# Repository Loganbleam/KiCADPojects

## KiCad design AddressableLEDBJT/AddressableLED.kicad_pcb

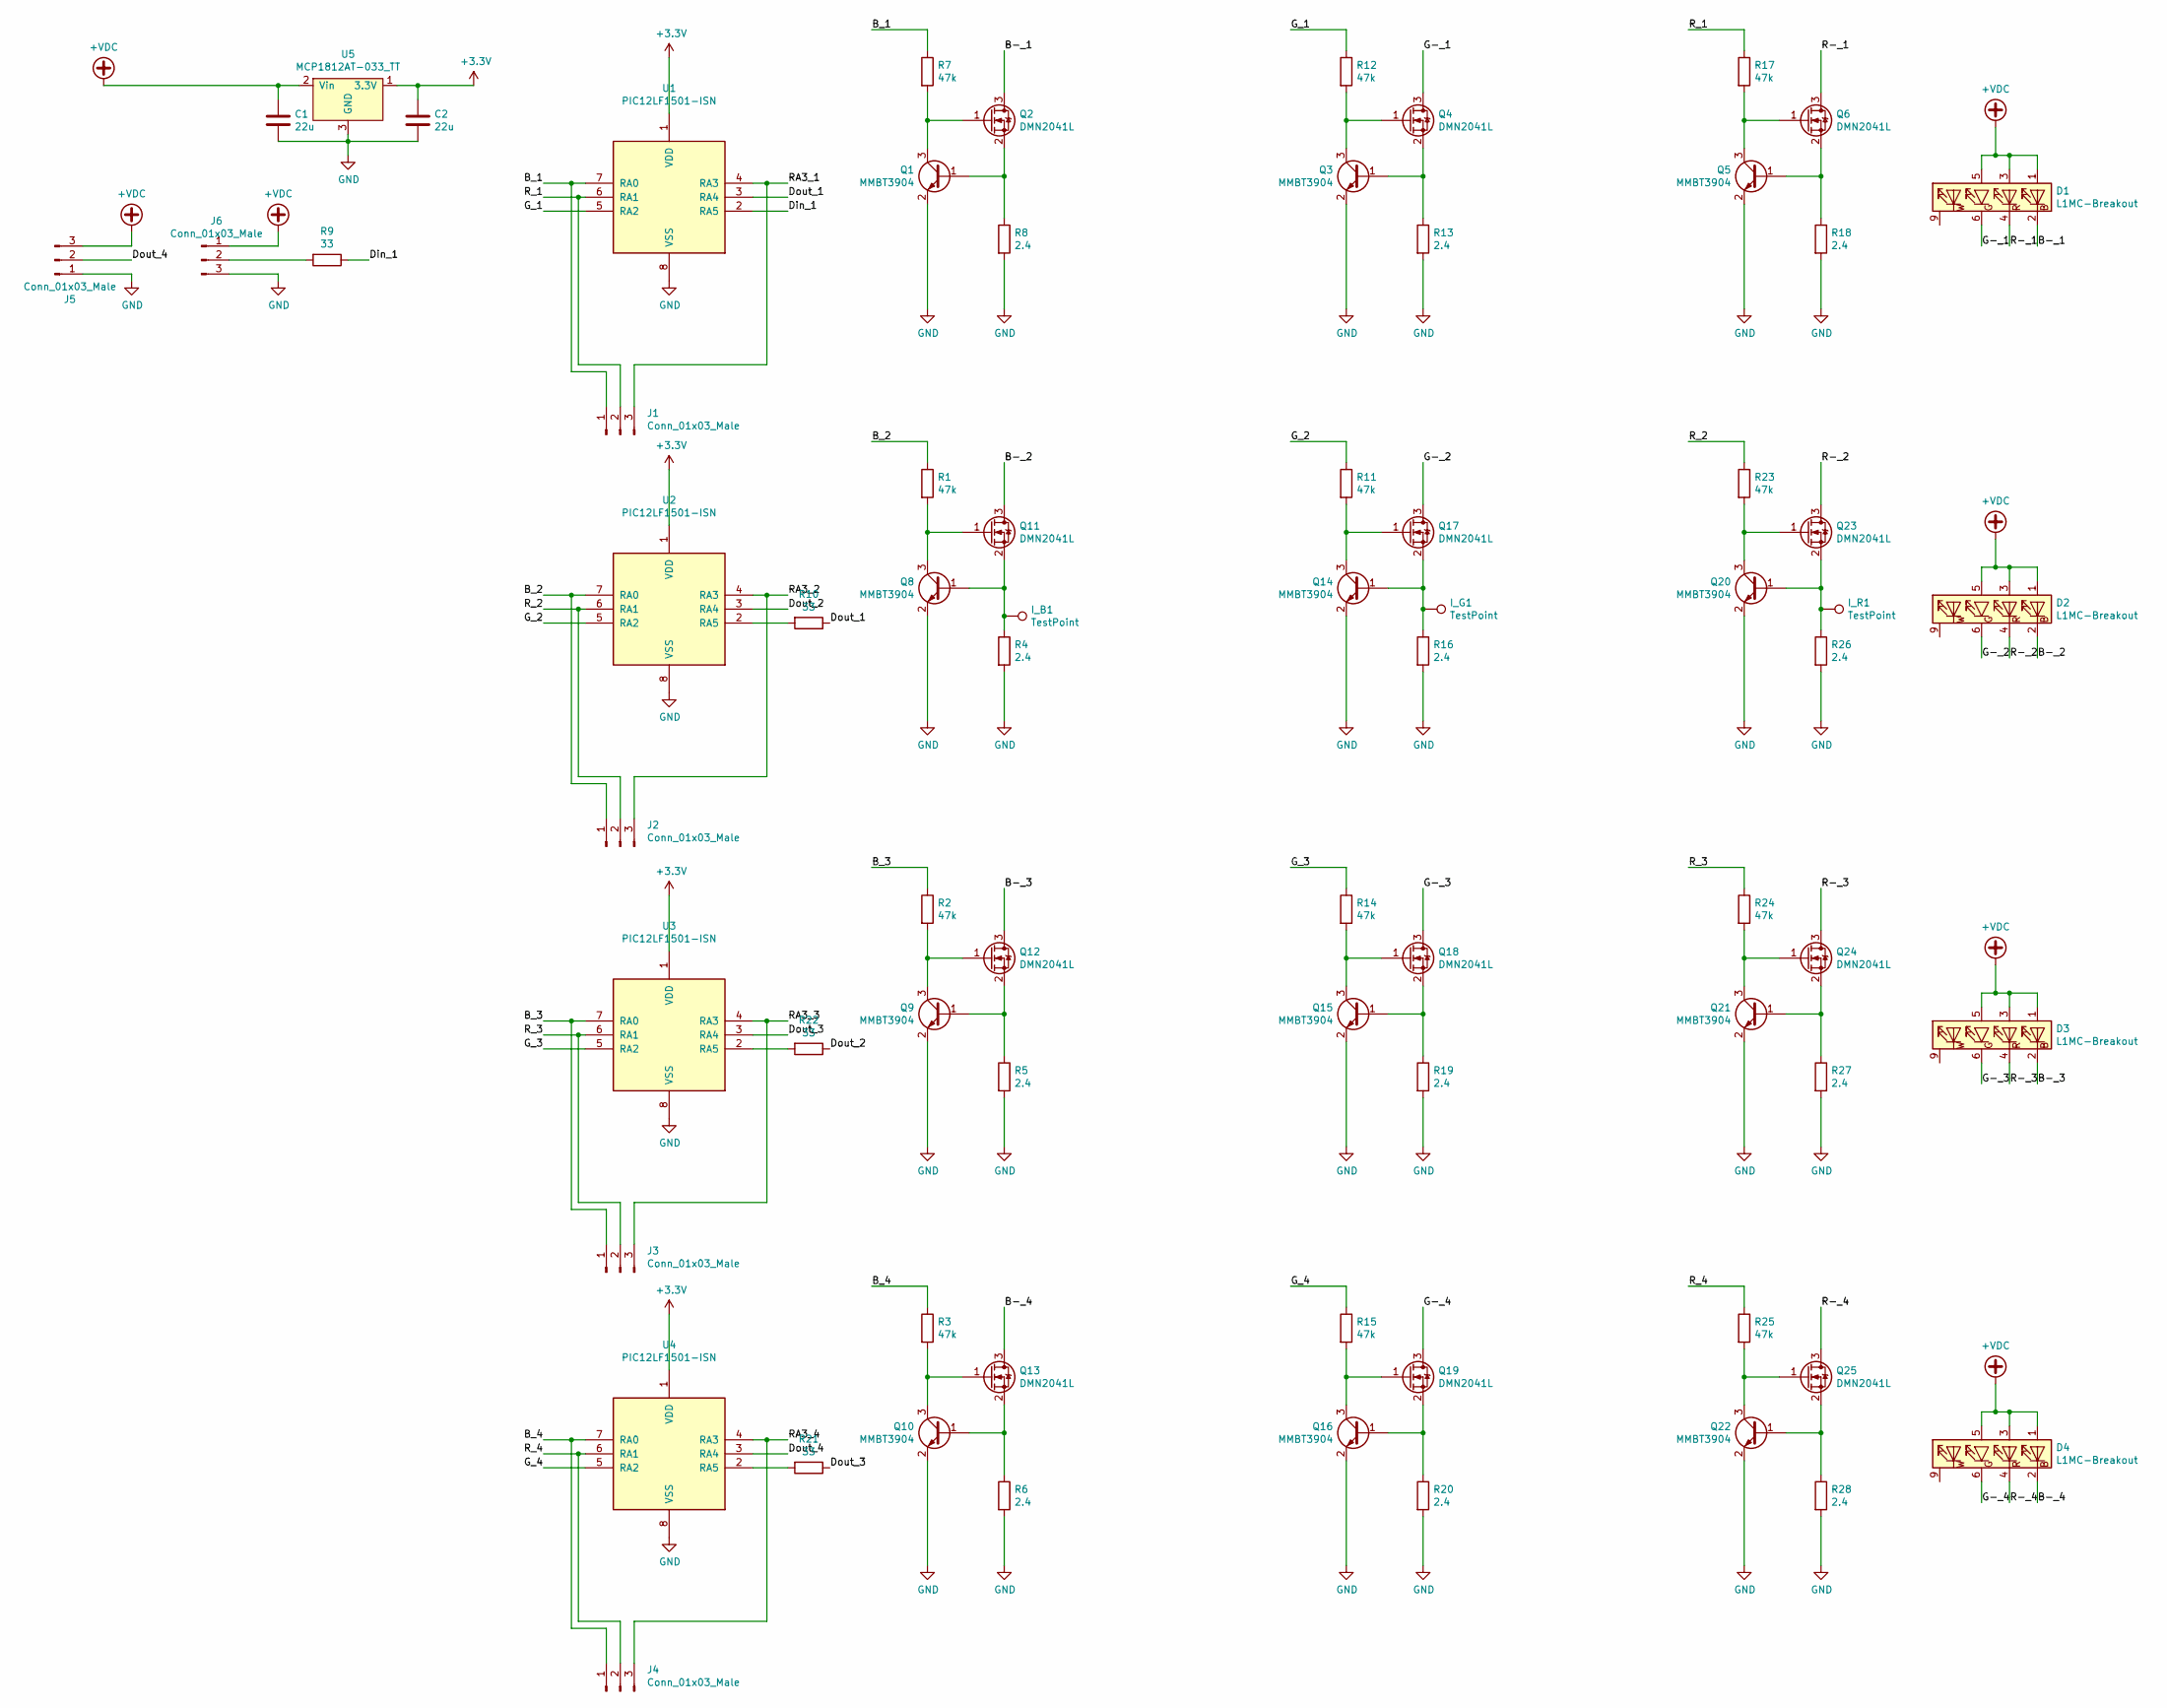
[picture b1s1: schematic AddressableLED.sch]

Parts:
C1, C2: 22u; C_0603_1608Metric
D1, D2, D3, D4: L1MC-Breakout; L1MC-RGB3080
I_B1: TestPoint; TestPoint_Pad_D1.0mm
I_G1: TestPoint; TestPoint_Pad_D1.0mm
I_R1: TestPoint; TestPoint_Pad_D1.0mm
J1, J2, J3, J4: Conn_01x03_Male; PinHeader_1x03_P1.00mm_Vertical
J5, J6: Conn_01x03_Male; JST_VH_B3P-VH-B_1x03_P3.96mm_Vertical
Q1, Q3, Q5, Q8, Q9, Q10, Q14, Q15, Q16, Q20, Q21, Q22: MMBT3904; SOT-23
Q2, Q4, Q6, Q11, Q12, Q13, Q17, Q18, Q19, Q23, Q24, Q25: DMN2041L; SOT-23
R1, R2, R3, R7, R11, R12, R14, R15, R17, R23, R24, R25: 47k; R_0603_1608Metric
R4, R5, R6, R8, R13, R16, R18, R19, R20, R26, R27, R28: 2.4; R_0805_2012Metric
R9, R10, R21, R22: 33; R_0603_1608Metric
U1, U2, U3, U4: PIC12LF1501-ISN; DFN-8-1EP_3x3mm_P0.65mm_EP1.7x2.05mm
U5: MCP1812AT-033_TT; SOT-23

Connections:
+3V3: C2.1, U1.1 (VDD), U2.1 (VDD), U3.1 (VDD), U4.1 (VDD), U5.1 (3.3V)
+VDC: C1.1, D1.1 (B+), D1.3 (R+), D1.5 (G+), D2.1 (B+), D2.3 (R+), D2.5 (G+), D3.1 (B+), D3.3 (R+), D3.5 (G+), D4.1 (B+), D4.3 (R+), D4.5 (G+), J5.3, J6.1, U5.2 (Vin)
/B-_1: D1.2 (B-), Q2.3 (D)
/B-_2: D2.2 (B-), Q11.3 (D)
/B-_3: D3.2 (B-), Q12.3 (D)
/B-_4: D4.2 (B-), Q13.3 (D)
/B_1: J1.1, R7.1, U1.7 (RA0)
/B_2: J2.1, R1.1, U2.7 (RA0)
/B_3: J3.1, R2.1, U3.7 (RA0)
/B_4: J4.1, R3.1, U4.7 (RA0)
/Din_1: R9.1, U1.2 (RA5)
/Dout_1: R10.1, U1.3 (RA4)
/Dout_2: R22.1, U2.3 (RA4)
/Dout_3: R21.1, U3.3 (RA4)
/Dout_4: J5.2, U4.3 (RA4)
/G-_1: D1.6 (G-), Q4.3 (D)
/G-_2: D2.6 (G-), Q17.3 (D)
/G-_3: D3.6 (G-), Q18.3 (D)
/G-_4: D4.6 (G-), Q19.3 (D)
/G_1: R12.1, U1.5 (RA2)
/G_2: R11.1, U2.5 (RA2)
/G_3: R14.1, U3.5 (RA2)
/G_4: R15.1, U4.5 (RA2)
/R-_1: D1.4 (R-), Q6.3 (D)
/R-_2: D2.4 (R-), Q23.3 (D)
/R-_3: D3.4 (R-), Q24.3 (D)
/R-_4: D4.4 (R-), Q25.3 (D)
/RA3_1: J1.3, U1.4 (RA3)
/RA3_2: J2.3, U2.4 (RA3)
/RA3_3: J3.3, U3.4 (RA3)
/RA3_4: J4.3, U4.4 (RA3)
/R_1: J1.2, R17.1, U1.6 (RA1)
/R_2: J2.2, R23.1, U2.6 (RA1)
/R_3: J3.2, R24.1, U3.6 (RA1)
/R_4: J4.2, R25.1, U4.6 (RA1)
GND: C1.2, C2.2, J5.1, J6.3, Q1.2 (E), Q3.2 (E), Q5.2 (E), Q8.2 (E), Q9.2 (E), Q10.2 (E), Q14.2 (E), Q15.2 (E), Q16.2 (E), Q20.2 (E), Q21.2 (E), Q22.2 (E), R4.2, R5.2, R6.2, R8.2, R13.2, R16.2, R18.2, R19.2, R20.2, R26.2, R27.2, R28.2, U1.8 (VSS), U2.8 (VSS), U3.8 (VSS), U4.8 (VSS), U5.3 (GND)
unnamed: I_B1.1, Q8.1 (B), Q11.2 (S), R4.1
unnamed: I_G1.1, Q14.1 (B), Q17.2 (S), R16.1
unnamed: I_R1.1, Q20.1 (B), Q23.2 (S), R26.1
unnamed: J6.2, R9.2
unnamed: Q1.1 (B), Q2.2 (S), R8.1
unnamed: Q1.3 (C), Q2.1 (G), R7.2
unnamed: Q3.1 (B), Q4.2 (S), R13.1
unnamed: Q3.3 (C), Q4.1 (G), R12.2
unnamed: Q5.1 (B), Q6.2 (S), R18.1
unnamed: Q5.3 (C), Q6.1 (G), R17.2
unnamed: Q10.1 (B), Q13.2 (S), R6.1
unnamed: Q10.3 (C), Q13.1 (G), R3.2
unnamed: Q8.3 (C), Q11.1 (G), R1.2
unnamed: Q9.3 (C), Q12.1 (G), R2.2
unnamed: Q9.1 (B), Q12.2 (S), R5.1
unnamed: Q14.3 (C), Q17.1 (G), R11.2
unnamed: Q15.1 (B), Q18.2 (S), R19.1
unnamed: Q15.3 (C), Q18.1 (G), R14.2
unnamed: Q16.1 (B), Q19.2 (S), R20.1
unnamed: Q16.3 (C), Q19.1 (G), R15.2
unnamed: Q20.3 (C), Q23.1 (G), R23.2
unnamed: Q21.1 (B), Q24.2 (S), R27.1
unnamed: Q21.3 (C), Q24.1 (G), R24.2
unnamed: Q22.1 (B), Q25.2 (S), R28.1
unnamed: Q22.3 (C), Q25.1 (G), R25.2
unnamed: R10.2, U2.2 (RA5)
unnamed: R21.2, U4.2 (RA5)
unnamed: R22.2, U3.2 (RA5)

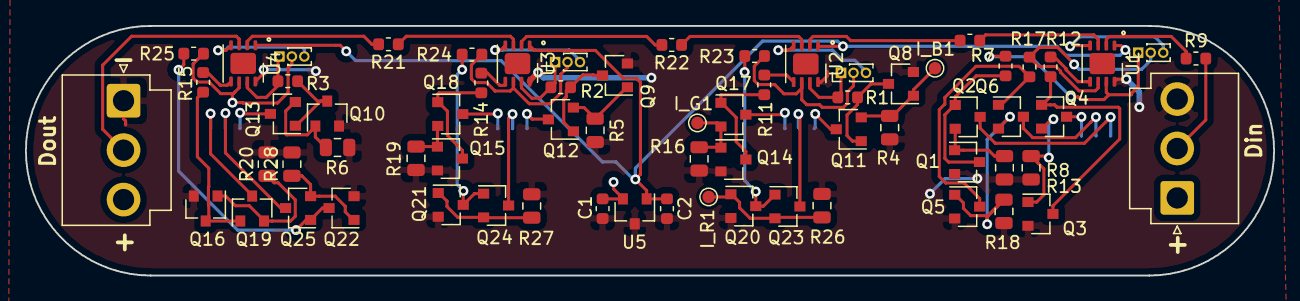
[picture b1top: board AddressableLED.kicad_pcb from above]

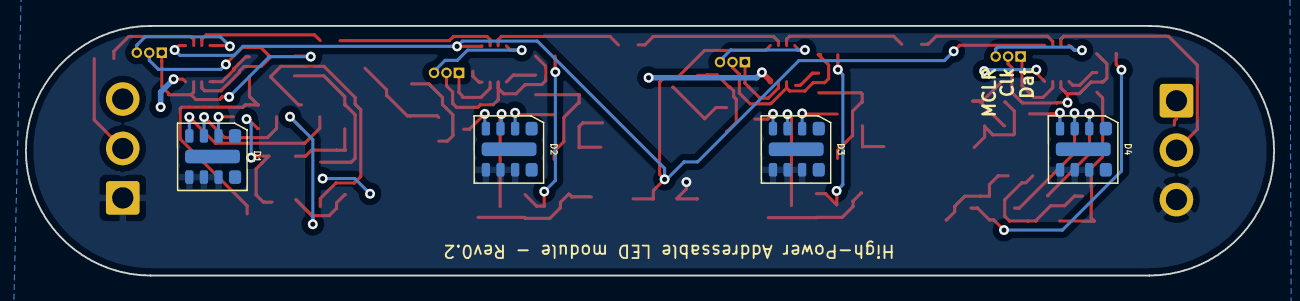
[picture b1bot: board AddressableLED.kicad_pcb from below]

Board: 2 copper layers, 100.0 x 20.0 mm, 72 parts (4 on the bottom side), 64 nets.

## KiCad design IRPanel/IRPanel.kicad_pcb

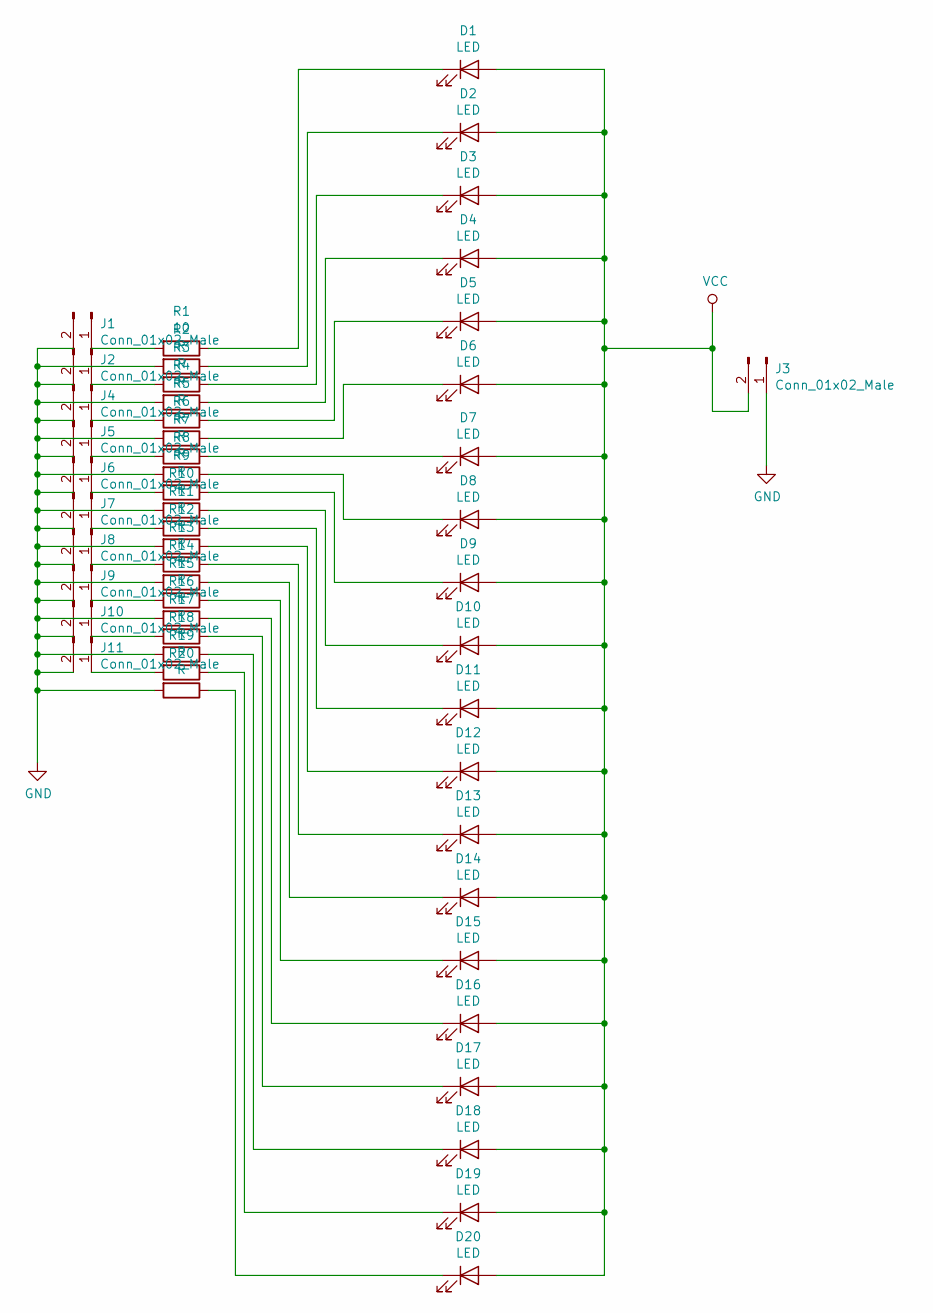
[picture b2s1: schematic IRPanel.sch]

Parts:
D1, D2, D3, D4, D5, D6, D7, D8, D9, D10, D11, D12, D13, D14, D15, D16, D17, D18, D19, D20: LED; IN-P281ASGIR
J1, J2, J4, J5, J6, J7, J8, J9, J10, J11: Conn_01x02_Male; PinHeader_1x02_P2.54mm_Vertical
J3: Conn_01x02_Male; TerminalBlock_Phoenix_PT-1,5-2-3.5-H_1x02_P3.50mm_Horizontal
R1: 10; R_0603_1608Metric
R2, R3, R4, R5, R6, R7, R8, R9, R10, R11, R12, R13, R14, R15, R16, R17, R18, R19, R20: R; R_0603_1608Metric

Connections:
GND: J1.2, J2.2, J3.1, J4.2, J5.2, J6.2, J7.2, J8.2, J9.2, J10.2, J11.2, R2.2, R4.2, R6.2, R8.2, R10.2, R12.2, R14.2, R16.2, R18.2, R20.2
unnamed: D1.1 (K), R1.1
unnamed: D2.1 (K), R2.1
unnamed: D3.1 (K), R3.1
unnamed: D4.1 (K), R4.1
unnamed: D5.1 (K), R5.1
unnamed: D6.1 (K), R6.1
unnamed: D7.1 (K), R7.1
unnamed: D8.1 (K), R8.1
unnamed: D9.1 (K), R9.1
unnamed: D10.1 (K), R10.1
unnamed: D11.1 (K), R11.1
unnamed: D12.1 (K), R12.1
unnamed: D13.1 (K), R13.1
unnamed: D14.1 (K), R14.1
unnamed: D15.1 (K), R15.1
unnamed: D16.1 (K), R16.1
unnamed: D17.1 (K), R17.1
unnamed: D18.1 (K), R18.1
unnamed: D19.1 (K), R19.1
unnamed: D20.1 (K), R20.1
unnamed: J1.1, R1.2
unnamed: J2.1, R3.2
unnamed: J4.1, R5.2
unnamed: J5.1, R7.2
unnamed: J6.1, R9.2
unnamed: J7.1, R11.2
unnamed: J8.1, R13.2
unnamed: J9.1, R15.2
unnamed: J10.1, R17.2
unnamed: J11.1, R19.2
VCC: D1.2 (A), D2.2 (A), D3.2 (A), D4.2 (A), D5.2 (A), D6.2 (A), D7.2 (A), D8.2 (A), D9.2 (A), D10.2 (A), D11.2 (A), D12.2 (A), D13.2 (A), D14.2 (A), D15.2 (A), D16.2 (A), D17.2 (A), D18.2 (A), D19.2 (A), D20.2 (A), J3.2

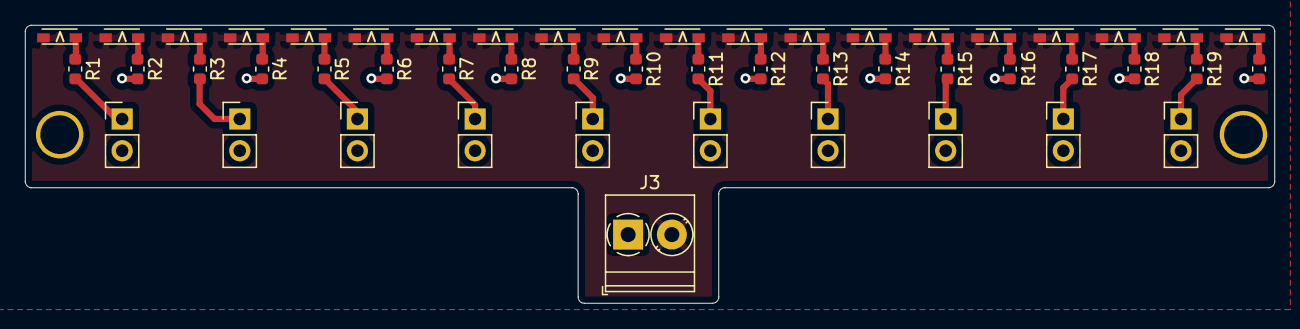
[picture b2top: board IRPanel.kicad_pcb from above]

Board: 2 copper layers, 100.0 x 22.2 mm, 51 parts (0 on the bottom side), 32 nets.

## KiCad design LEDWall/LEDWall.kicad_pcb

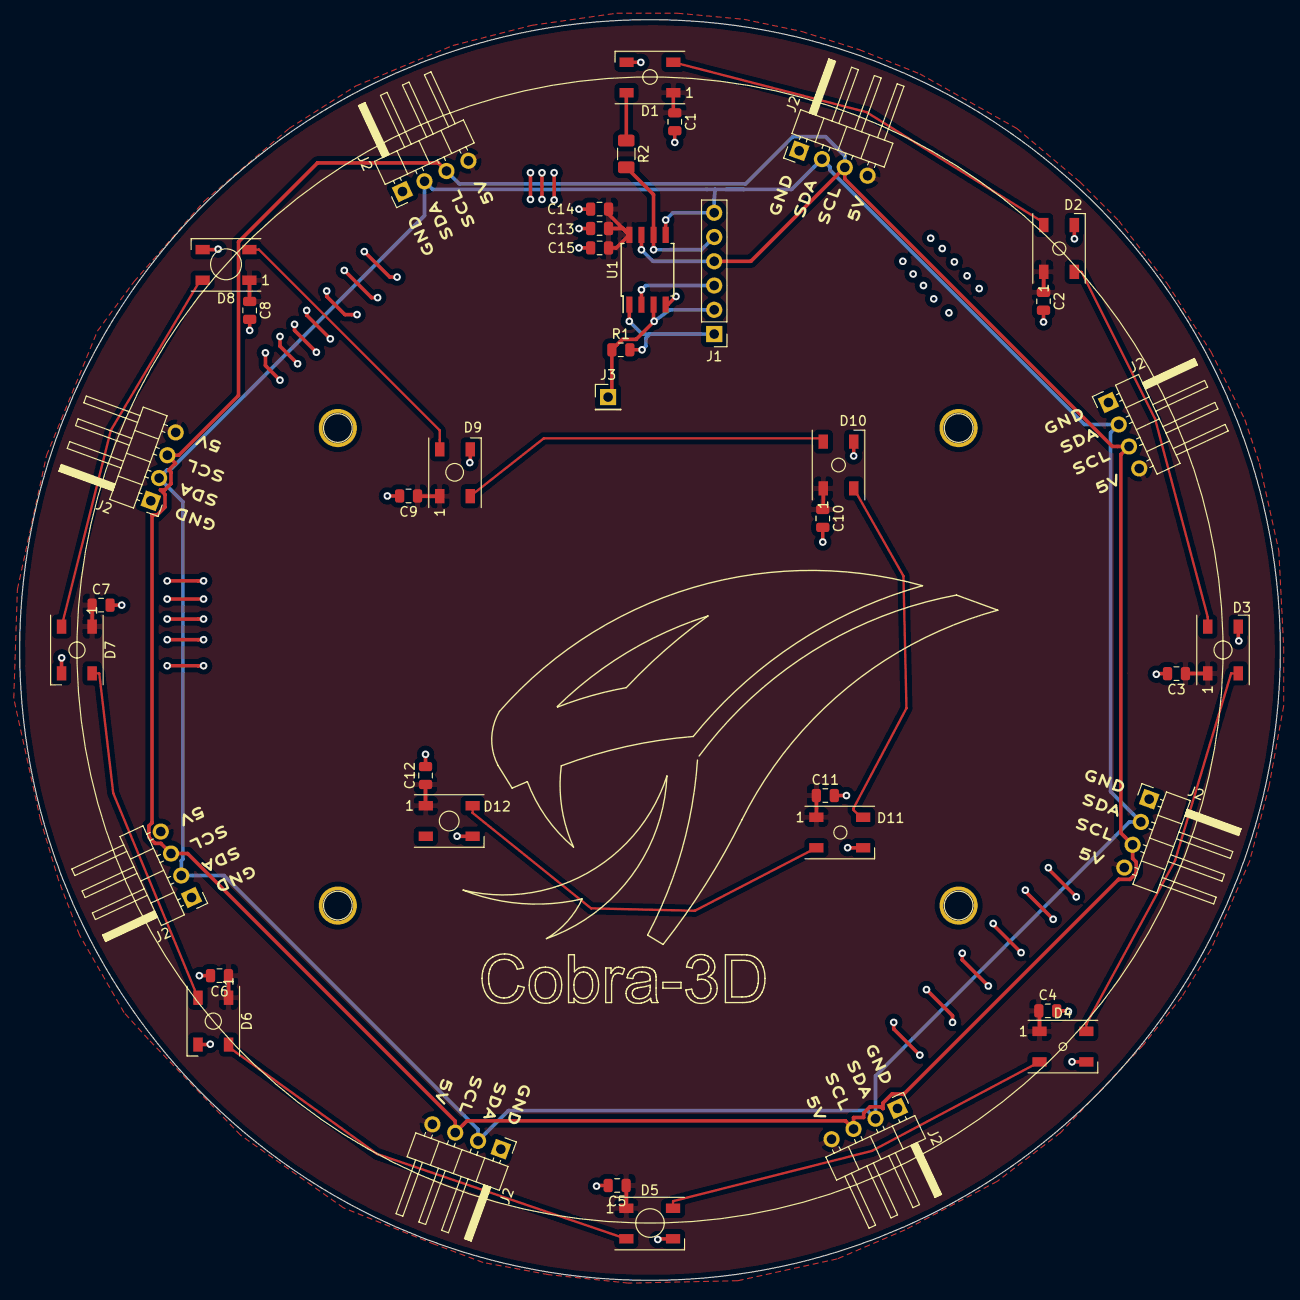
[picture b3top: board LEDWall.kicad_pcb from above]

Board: 2 copper layers, 132.0 x 132.0 mm, 40 parts (0 on the bottom side), 20 nets.

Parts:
C1, C2, C3, C4, C5, C6, C7, C8, C9, C10, C11, C12, C13, C14, C15: 10u; C_0805_2012Metric
D1, D2, D3, D4, D5, D6, D7, D8, D9, D10, D11, D12: WS2812B; LED_WS2812B_PLCC4_5.0x5.0mm_P3.2mm
J1: Conn_01x06_Male; PinHeader_1x06_P2.54mm_Vertical
J2, J2#2, J2#3, J2#4, J2#5, J2#6, J2#7, J2#8: Conn_01x04_Male; PinHeader_1x04_P2.54mm_Horizontal
J3: Conn_01x01_Male; PinHeader_1x01_P2.54mm_Vertical
R1: 2M; R_0805_2012Metric
R2: R; R_1206_3216Metric
U1: ATtiny85-20SU; SOIJ-8_5.3x5.3mm_P1.27mm

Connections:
+5V: C1.1, C2.1, C3.1, C4.1, C5.1, C6.1, C7.1, C8.1, C9.1, C10.1, C11.1, C12.1, C13.1, C14.1, C15.1, D1.1, D2.1, D3.1, D4.1, D5.1, D6.1, D7.1, D8.1, D9.1, D10.1, D11.1, D12.1, J2.4, J2#2.4, J2#3.4, J2#4.4, J2#5.4, J2#6.4, J2#7.4, J2#8.4, U1.8
/SCL: J1.4, J2.3, J2#2.3, J2#3.3, J2#4.3, J2#5.3, J2#6.3, J2#7.3, J2#8.3, U1.7
/SDA: J1.6, J2.2, J2#2.2, J2#3.2, J2#4.2, J2#5.2, J2#6.2, J2#7.2, J2#8.2, U1.5
GND: C1.2, C2.2, C3.2, C4.2, C5.2, C6.2, C7.2, C8.2, C9.2, C10.2, C11.2, C12.2, C13.2, C14.2, C15.2, D1.3, D2.3, D3.3, D4.3, D5.3, D6.3, D7.3, D8.3, D9.3, D10.3, D11.3, D12.3, J2.1, J2#2.1, J2#3.1, J2#4.1, J2#5.1, J2#6.1, J2#7.1, J2#8.1, U1.4
unnamed: D1.2, D2.4
unnamed: D1.4, R2.1
unnamed: D2.2, D3.4
unnamed: D3.2, D4.4
unnamed: D4.2, D5.4
unnamed: D5.2, D6.4
unnamed: D6.2, D7.4
unnamed: D7.2, D8.4
unnamed: D8.2, D9.4
unnamed: D10.2, D11.4
unnamed: D9.2, D10.4
unnamed: D11.2, D12.4
unnamed: J1.1, R1.2, U1.1
unnamed: J1.2, J3.1, R1.1, U1.3
unnamed: J1.3, U1.2
unnamed: J1.5, R2.2, U1.6
